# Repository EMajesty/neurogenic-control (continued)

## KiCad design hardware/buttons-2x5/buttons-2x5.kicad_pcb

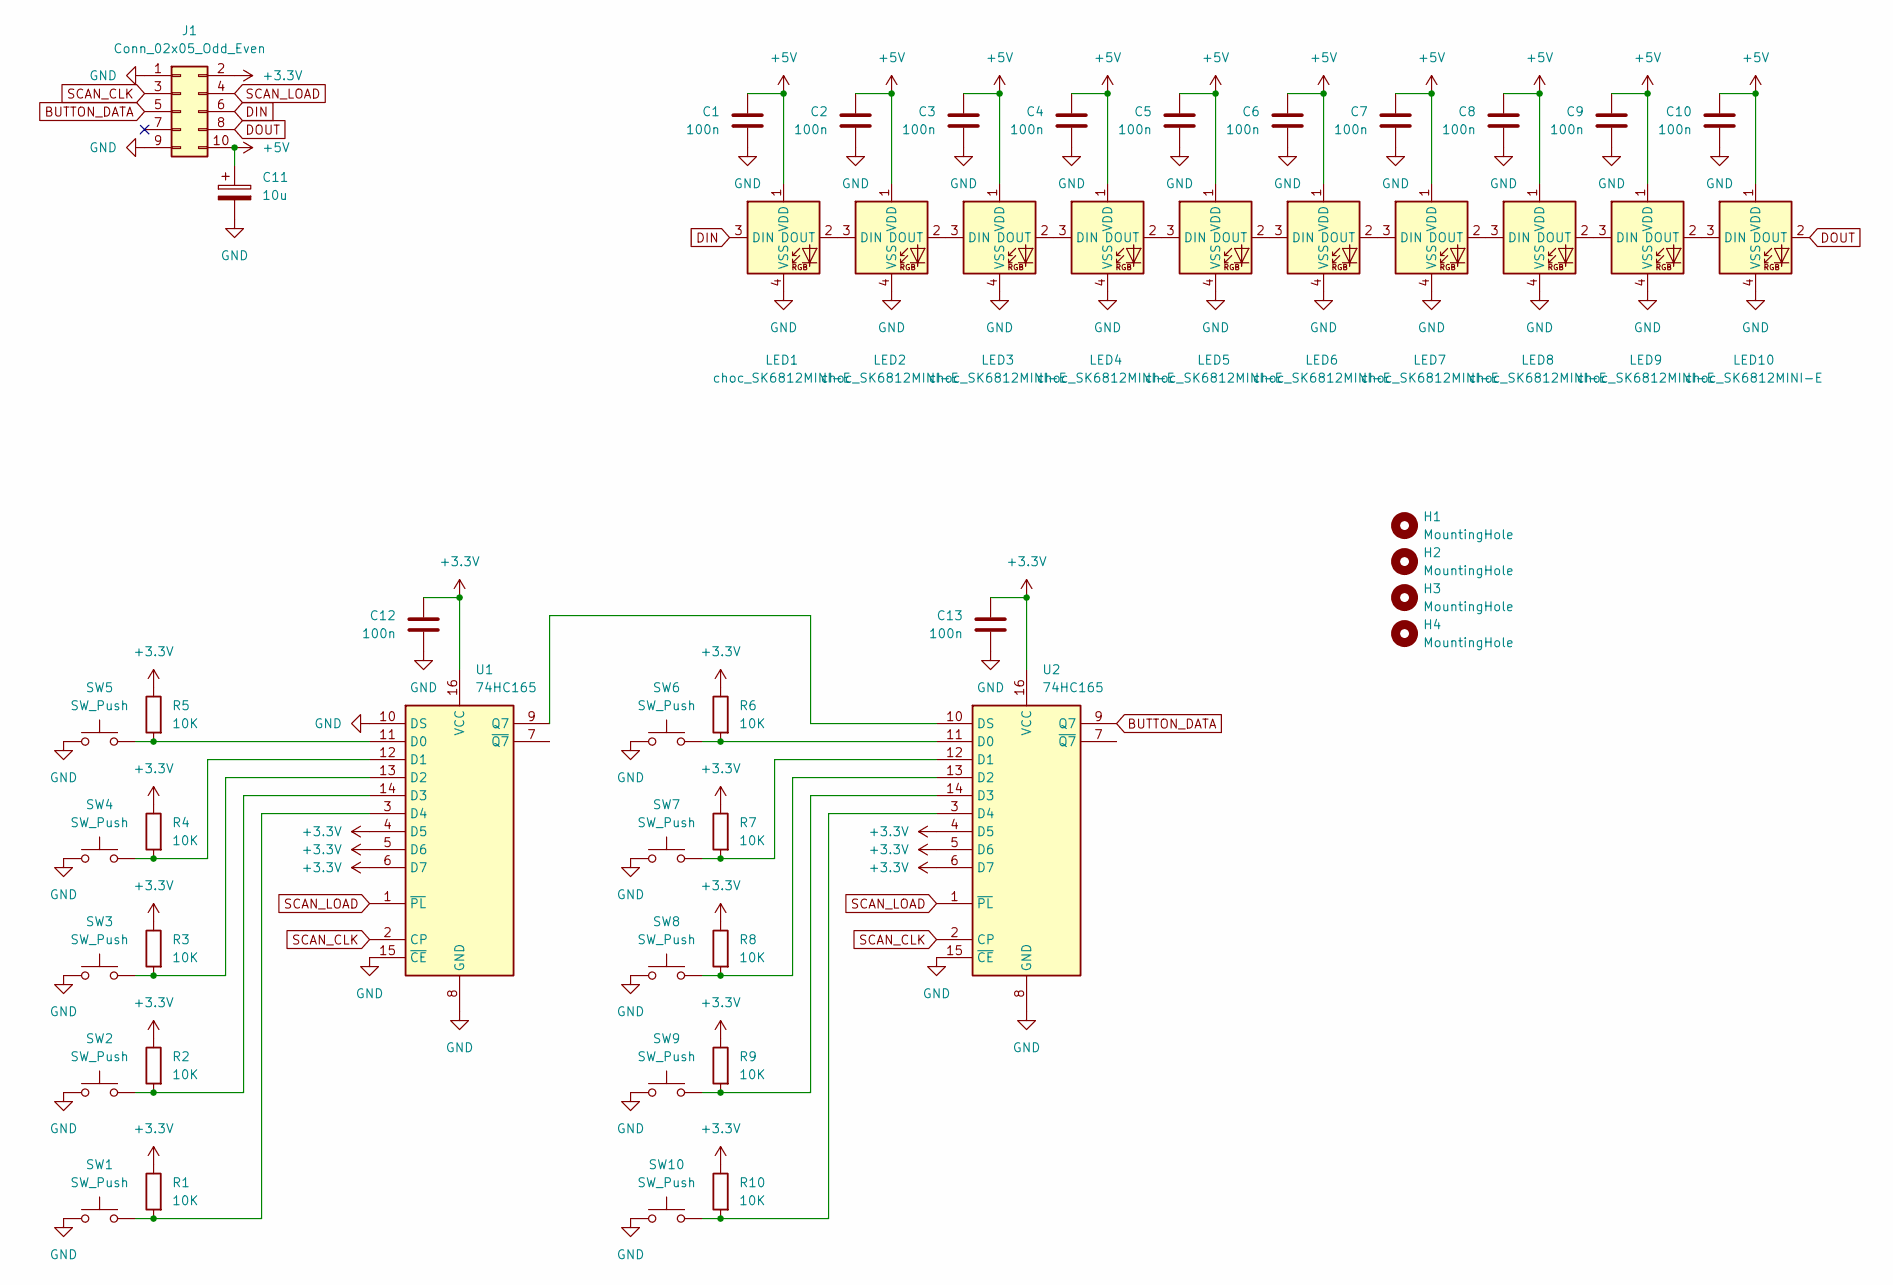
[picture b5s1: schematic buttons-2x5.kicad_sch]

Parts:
C1, C2, C3, C4, C5, C6, C7, C8, C9, C10, C12, C13: 100n; C_0805_2012Metric_Pad1.18x1.45mm_HandSolder
C11: 10u; CP_Radial_D4.0mm_P2.00mm
H1, H2, H3, H4: MountingHole; MountingHole_3.2mm_M3
J1: Conn_02x05_Odd_Even; IDC-Header_2x05_P2.54mm_Vertical
LED1, LED2, LED3, LED4, LED5, LED6, LED7, LED8, LED9, LED10: choc_SK6812MINI-E; LED_choc_6028R-ROT
R1, R2, R3, R4, R5, R6, R7, R8, R9, R10: 10K; R_0805_2012Metric_Pad1.20x1.40mm_HandSolder
SW1, SW2, SW3, SW4, SW5, SW6, SW7, SW8, SW9, SW10: SW_Push; SW_choc_v1_1u
U1, U2: 74HC165; SOIC-16_3.9x9.9mm_P1.27mm

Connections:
+3.3V: C12.1, C13.1, J1.2, R1.1, R2.1, R3.1, R4.1, R5.1, R6.1, R7.1, R8.1, R9.1, R10.1, U1.4 (D5), U1.5 (D6), U1.6 (D7), U1.16 (VCC), U2.4 (D5), U2.5 (D6), U2.6 (D7), U2.16 (VCC)
+5V: C1.1, C2.1, C3.1, C4.1, C5.1, C6.1, C7.1, C8.1, C9.1, C10.1, C11.1, J1.10, LED1.1 (VDD), LED2.1 (VDD), LED3.1 (VDD), LED4.1 (VDD), LED5.1 (VDD), LED6.1 (VDD), LED7.1 (VDD), LED8.1 (VDD), LED9.1 (VDD), LED10.1 (VDD)
BUTTON_DATA: J1.5, U2.9 (Q7)
DIN: J1.6, LED1.3 (DIN)
DOUT: J1.8, LED10.2 (DOUT)
GND: C1.2, C2.2, C3.2, C4.2, C5.2, C6.2, C7.2, C8.2, C9.2, C10.2, C11.2, C12.2, C13.2, J1.1, J1.9, LED1.4 (VSS), LED2.4 (VSS), LED3.4 (VSS), LED4.4 (VSS), LED5.4 (VSS), LED6.4 (VSS), LED7.4 (VSS), LED8.4 (VSS), LED9.4 (VSS), LED10.4 (VSS), SW1.2, SW2.2, SW3.2, SW4.2, SW5.2, SW6.2, SW7.2, SW8.2, SW9.2, SW10.2, U1.8 (GND), U1.10 (DS), U1.15 (~CE), U2.8 (GND), U2.15 (~CE)
unnamed: LED1.2 (DOUT), LED2.3 (DIN)
unnamed: LED2.2 (DOUT), LED3.3 (DIN)
unnamed: LED3.2 (DOUT), LED4.3 (DIN)
unnamed: LED4.2 (DOUT), LED5.3 (DIN)
unnamed: LED5.2 (DOUT), LED6.3 (DIN)
unnamed: LED6.2 (DOUT), LED7.3 (DIN)
unnamed: LED7.2 (DOUT), LED8.3 (DIN)
unnamed: LED8.2 (DOUT), LED9.3 (DIN)
unnamed: LED9.2 (DOUT), LED10.3 (DIN)
unnamed: R5.2, SW5.1, U1.11 (D0)
unnamed: R4.2, SW4.1, U1.12 (D1)
unnamed: R3.2, SW3.1, U1.13 (D2)
unnamed: R2.2, SW2.1, U1.14 (D3)
unnamed: R1.2, SW1.1, U1.3 (D4)
unnamed: U1.9 (Q7), U2.10 (DS)
unnamed: R6.2, SW6.1, U2.11 (D0)
unnamed: R7.2, SW7.1, U2.12 (D1)
unnamed: R8.2, SW8.1, U2.13 (D2)
unnamed: R9.2, SW9.1, U2.14 (D3)
unnamed: R10.2, SW10.1, U2.3 (D4)
SCAN_CLK: J1.3, U1.2 (CP), U2.2 (CP)
SCAN_LOAD: J1.4, U1.1 (~PL), U2.1 (~PL)

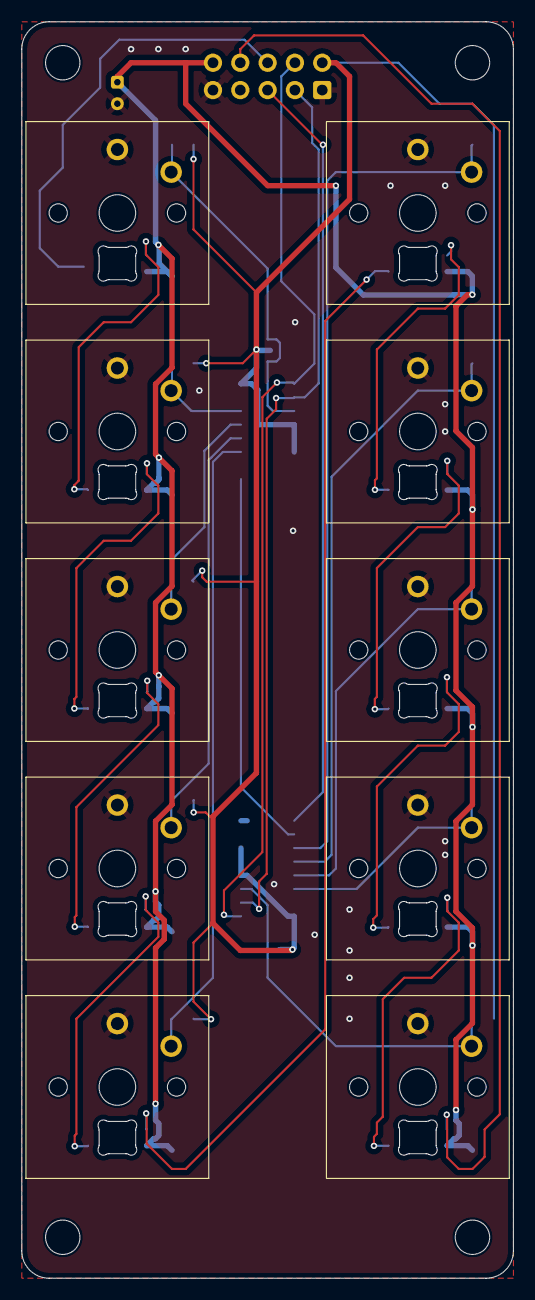
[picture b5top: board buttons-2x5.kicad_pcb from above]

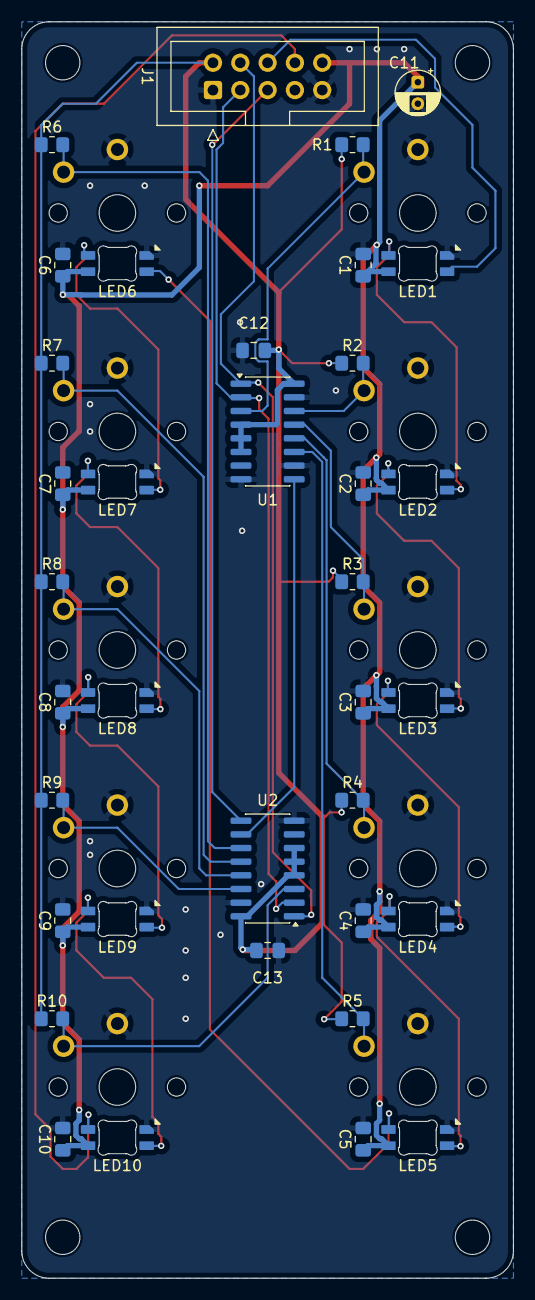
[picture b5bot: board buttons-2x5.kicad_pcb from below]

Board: 2 copper layers, 45.7 x 116.8 mm, 50 parts (36 on the bottom side), 28 nets.

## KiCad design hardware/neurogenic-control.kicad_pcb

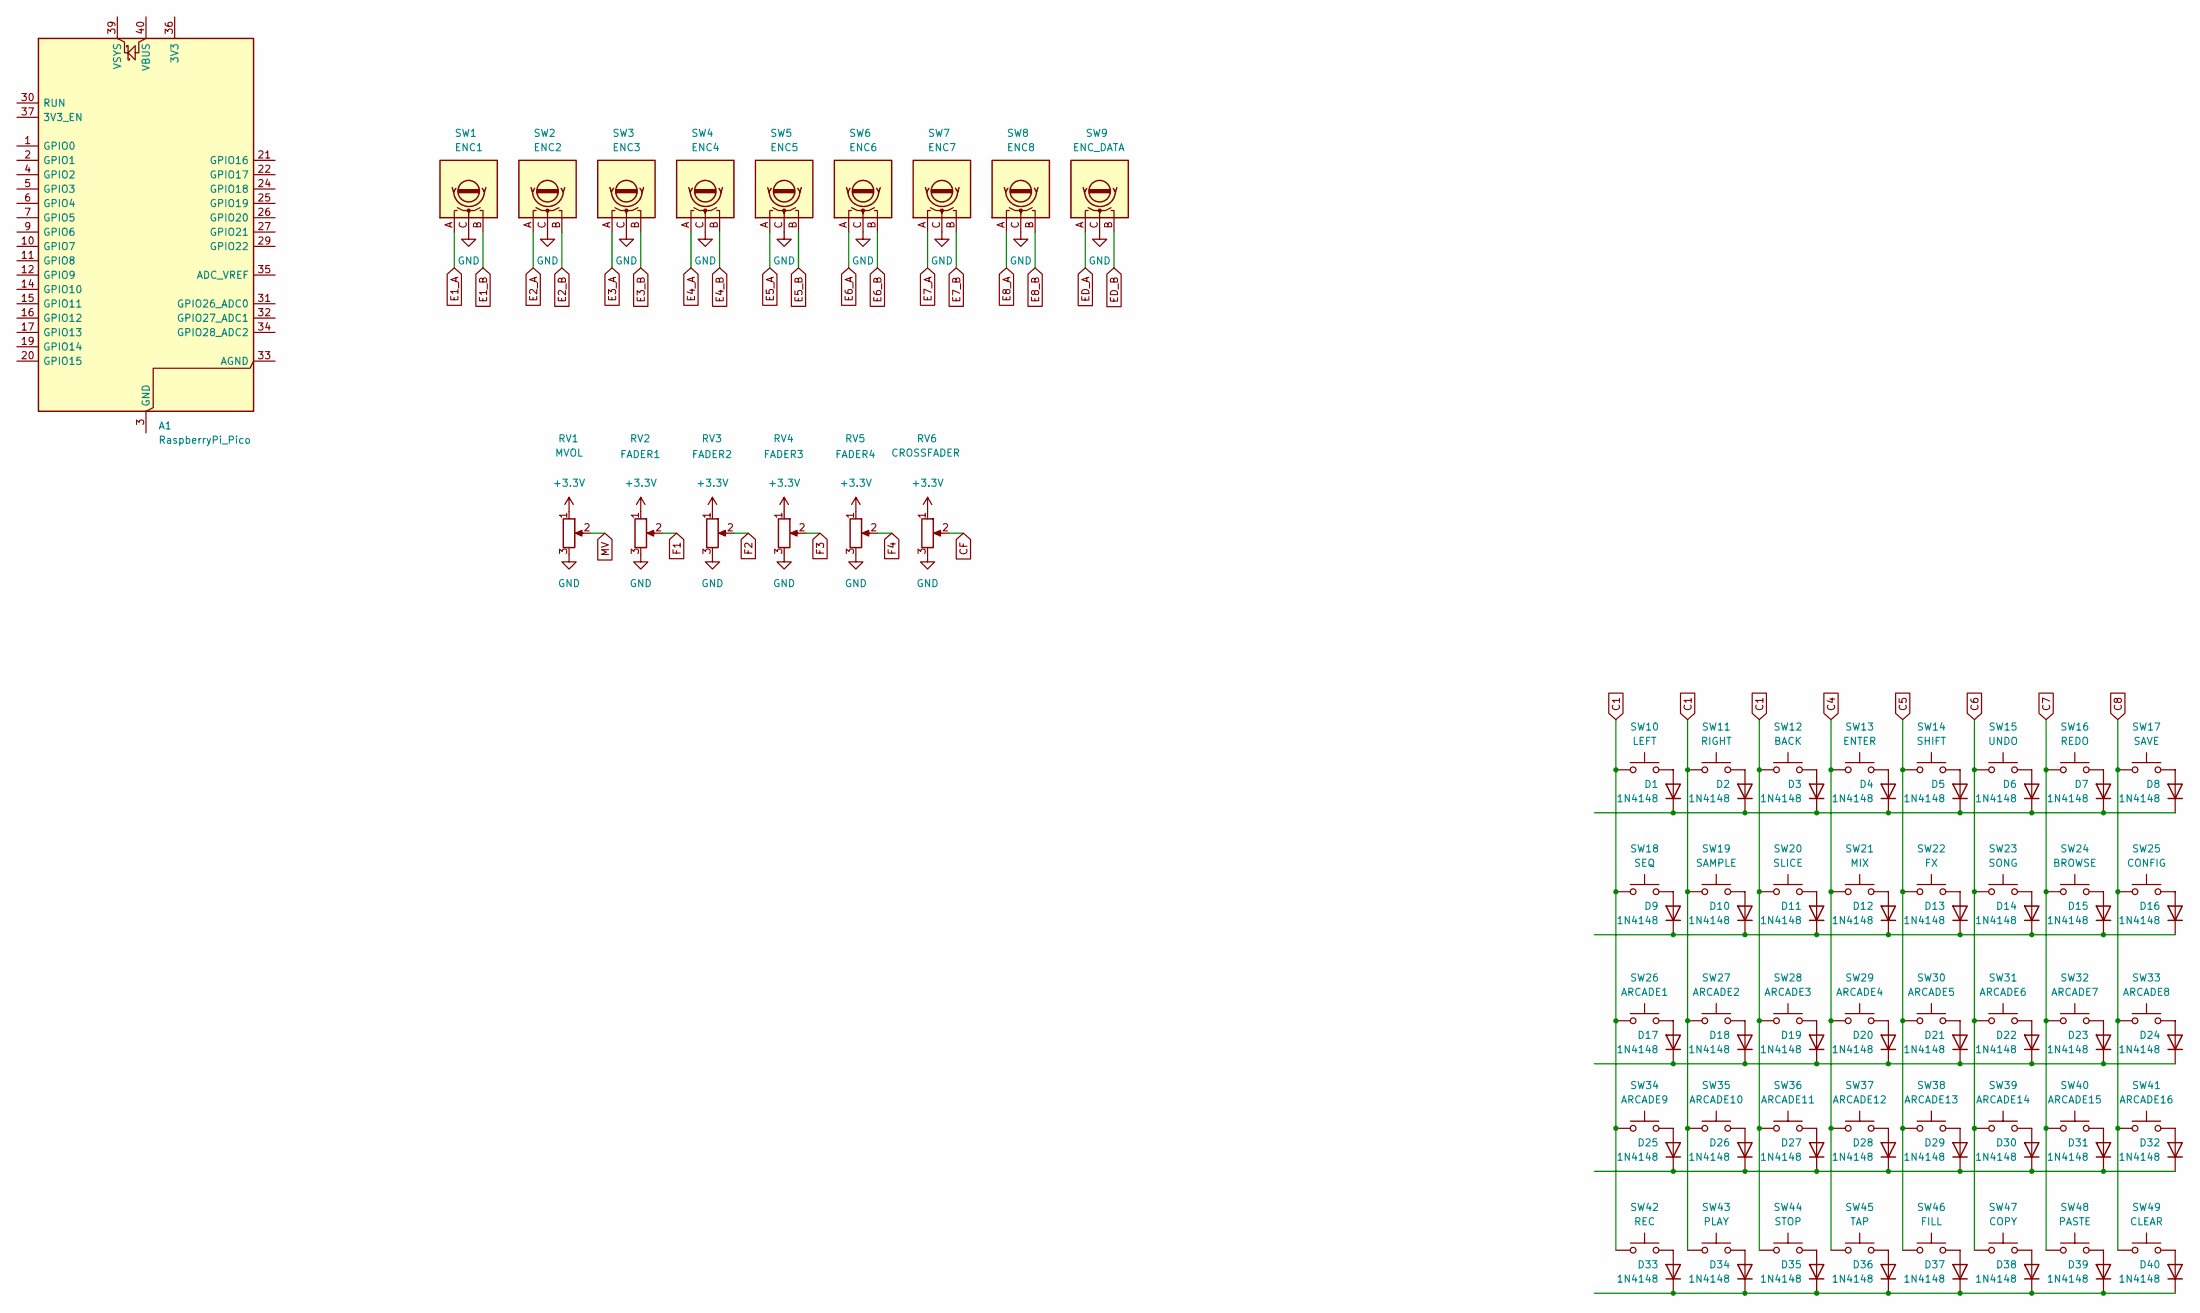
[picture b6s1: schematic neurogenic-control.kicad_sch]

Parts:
A1: RaspberryPi_Pico; RaspberryPi_Pico_Common_Unspecified
D1, D2, D3, D4, D5, D6, D7, D8, D9, D10, D11, D12, D13, D14, D15, D16, D17, D18, D19, D20, D21, D22, D23, D24, D25, D26, D27, D28, D29, D30, D31, D32, D33, D34, D35, D36, D37, D38, D39, D40: 1N4148; D_DO-35_SOD27_P7.62mm_Horizontal
RV1: MVOL
RV2: FADER1
RV3: FADER2
RV4: FADER3
RV5: FADER4
RV6: CROSSFADER
SW1: ENC1; RotaryEncoder_Alps_EC12E_Vertical_H20mm
SW2: ENC2; RotaryEncoder_Alps_EC12E_Vertical_H20mm
SW3: ENC3; RotaryEncoder_Alps_EC12E_Vertical_H20mm
SW4: ENC4; RotaryEncoder_Alps_EC12E_Vertical_H20mm
SW5: ENC5; RotaryEncoder_Alps_EC12E_Vertical_H20mm
SW6: ENC6; RotaryEncoder_Alps_EC12E_Vertical_H20mm
SW7: ENC7; RotaryEncoder_Alps_EC12E_Vertical_H20mm
SW8: ENC8; RotaryEncoder_Alps_EC12E_Vertical_H20mm
SW9: ENC_DATA; RotaryEncoder_Alps_EC12E_Vertical_H20mm
SW10: LEFT; SW_PG1350
SW11: RIGHT; SW_PG1350
SW12: BACK; SW_PG1350
SW13: ENTER; SW_PG1350
SW14: SHIFT; SW_PG1350
SW15: UNDO; SW_PG1350
SW16: REDO; SW_PG1350
SW17: SAVE; SW_PG1350
SW18: SEQ; SW_PG1350
SW19: SAMPLE; SW_PG1350
SW20: SLICE; SW_PG1350
SW21: MIX; SW_PG1350
SW22: FX; SW_PG1350
SW23: SONG; SW_PG1350
SW24: BROWSE; SW_PG1350
SW25: CONFIG; SW_PG1350
SW26: ARCADE1; Arcade_Button_24mm
SW27: ARCADE2; Arcade_Button_24mm
SW28: ARCADE3; Arcade_Button_24mm
SW29: ARCADE4; Arcade_Button_24mm
SW30: ARCADE5; Arcade_Button_24mm
SW31: ARCADE6; Arcade_Button_24mm
SW32: ARCADE7; Arcade_Button_24mm
SW33: ARCADE8; Arcade_Button_24mm
SW34: ARCADE9; Arcade_Button_24mm
SW35: ARCADE10; Arcade_Button_24mm
SW36: ARCADE11; Arcade_Button_24mm
SW37: ARCADE12; Arcade_Button_24mm
SW38: ARCADE13; Arcade_Button_24mm
SW39: ARCADE14; Arcade_Button_24mm
SW40: ARCADE15; Arcade_Button_24mm
SW41: ARCADE16; Arcade_Button_24mm
SW42: REC; SW_PG1350
SW43: PLAY; SW_PG1350
SW44: STOP; SW_PG1350
SW45: TAP; SW_PG1350
SW46: FILL; SW_PG1350
SW47: COPY; SW_PG1350
SW48: PASTE; SW_PG1350
SW49: CLEAR; SW_PG1350

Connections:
C1: SW10.1, SW11.1, SW12.1, SW18.1, SW19.1, SW20.1, SW26.1, SW27.1, SW28.1, SW34.1, SW35.1, SW36.1, SW42.1, SW43.1, SW44.1
C4: SW13.1, SW21.1, SW29.1, SW37.1, SW45.1
C5: SW14.1, SW22.1, SW30.1, SW38.1, SW46.1
C6: SW15.1, SW23.1, SW31.1, SW39.1, SW47.1
C7: SW16.1, SW24.1, SW32.1, SW40.1, SW48.1
C8: SW17.1, SW25.1, SW33.1, SW41.1, SW49.1
E1_A: SW1.A
E1_B: SW1.B
E2_A: SW2.A
E2_B: SW2.B
E3_A: SW3.A
E3_B: SW3.B
E4_A: SW4.A
E4_B: SW4.B
E5_A: SW5.A
E5_B: SW5.B
E6_A: SW6.A
E6_B: SW6.B
E7_A: SW7.A
E7_B: SW7.B
E8_A: SW8.A
E8_B: SW8.B
ED_A: SW9.A
ED_B: SW9.B
GND: RV1.3, RV2.3, RV3.3, RV4.3, RV5.3, RV6.3, SW1.C, SW2.C, SW3.C, SW4.C, SW5.C, SW6.C, SW7.C, SW8.C, SW9.C
unnamed: A1.3 (GND), A1.8 (GND), A1.13 (GND), A1.18 (GND), A1.23 (GND), A1.28 (GND), A1.38 (GND)
unnamed: D1.2 (A), SW10.2
unnamed: D1.1 (K), D2.1 (K), D3.1 (K), D4.1 (K), D5.1 (K), D6.1 (K), D7.1 (K), D8.1 (K)
unnamed: D2.2 (A), SW11.2
unnamed: D3.2 (A), SW12.2
unnamed: D4.2 (A), SW13.2
unnamed: D5.2 (A), SW14.2
unnamed: D6.2 (A), SW15.2
unnamed: D7.2 (A), SW16.2
unnamed: D8.2 (A), SW17.2
unnamed: D9.2 (A), SW18.2
unnamed: D10.2 (A), SW19.2
unnamed: D9.1 (K), D10.1 (K), D11.1 (K), D12.1 (K), D13.1 (K), D14.1 (K), D15.1 (K), D16.1 (K)
unnamed: D11.2 (A), SW20.2
unnamed: D12.2 (A), SW21.2
unnamed: D13.2 (A), SW22.2
unnamed: D14.2 (A), SW23.2
unnamed: D15.2 (A), SW24.2
unnamed: D16.2 (A), SW25.2
unnamed: D17.2 (A), SW26.2
unnamed: D17.1 (K), D18.1 (K), D19.1 (K), D20.1 (K), D21.1 (K), D22.1 (K), D23.1 (K), D24.1 (K)
unnamed: D18.2 (A), SW27.2
unnamed: D19.2 (A), SW28.2
unnamed: D20.2 (A), SW29.2
unnamed: D21.2 (A), SW30.2
unnamed: D22.2 (A), SW31.2
unnamed: D23.2 (A), SW32.2
unnamed: D24.2 (A), SW33.2
unnamed: D25.2 (A), SW34.2
unnamed: D25.1 (K), D26.1 (K), D27.1 (K), D28.1 (K), D29.1 (K), D30.1 (K), D31.1 (K), D32.1 (K)
unnamed: D26.2 (A), SW35.2
unnamed: D27.2 (A), SW36.2
unnamed: D28.2 (A), SW37.2
unnamed: D29.2 (A), SW38.2
unnamed: D30.2 (A), SW39.2
unnamed: D31.2 (A), SW40.2
unnamed: D32.2 (A), SW41.2
unnamed: D33.2 (A), SW42.2
unnamed: D33.1 (K), D34.1 (K), D35.1 (K), D36.1 (K), D37.1 (K), D38.1 (K), D39.1 (K), D40.1 (K)
unnamed: D34.2 (A), SW43.2
unnamed: D35.2 (A), SW44.2
unnamed: D36.2 (A), SW45.2
unnamed: D37.2 (A), SW46.2
unnamed: D38.2 (A), SW47.2
unnamed: D39.2 (A), SW48.2
unnamed: D40.2 (A), SW49.2
unnamed: RV1.1, RV2.1, RV3.1, RV4.1, RV5.1, RV6.1

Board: 2 copper layers, 90 parts (0 on the bottom side), 53 nets, no tracks yet.

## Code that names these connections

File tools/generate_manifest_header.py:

#!/usr/bin/env python3
"""Deterministically generate/check the firmware hardware header."""
import argparse, hashlib, json, pathlib, sys
ROOT=pathlib.Path(__file__).resolve().parents[1]
MANIFEST=ROOT/'hardware/manifest.json'; OUTPUT=ROOT/'firmware/generated/hardware_manifest.hpp'
GPIO_KEYS=('SCAN_CLK','SCAN_LOAD','BUTTON_DATA1','BUTTON_DATA2','BUTTON_DATA3','BUTTON_DATA4','BUTTON_DATA5','BUTTON_DATA6','BUTTON_DATA7','BUTTON_DATA8','BUTTON_DATA9','ENC_LED_DATA','RGB_DATA_RAW','ENC_LED_LATCH','ENC_LED_BLANK')
def validate(m):
    errors=[]
    if m.get('schema_version')!=1: errors.append('schema_version must be 1')
    for key in GPIO_KEYS:
        if not isinstance(m.get('gpio',{}).get(key),int): errors.append(f'missing integer gpio.{key}')
    if len(set(m.get('gpio',{}).values())) != len(m.get('gpio',{})): errors.append('GPIO assignments overlap')
    expected={'buttons-1x8':8,'buttons-2x5':16,'nav':8,'pads':16,'encoders':24}
    for board,bits in expected.items():
        regs=m.get('board_types',{}).get(board,{}).get('registers',[])
        if len(regs)*8!=bits or any(len(r.get('bits',[]))!=8 for r in regs): errors.append(f'{board} chain must contain {bits} bits')
    if m.get('board_types',{}).get('encoders',{}).get('tlc5947',{}).get('bits_per_frame')!=288: errors.append('TLC frame must be 288 bits')
    if errors: raise ValueError('\n'.join(errors))
def render(m):
    fingerprint=hashlib.sha256(MANIFEST.read_bytes()).hexdigest()
    g=m['gpio']; data=[g[f'BUTTON_DATA{i}'] for i in range(1,10)]
    outputs=m['board_types']['encoders']['tlc5947']['outputs']; by_name={name:i for i,name in enumerate(outputs)}
    encoder_map=[[by_name[f'{c}{i}'] for c in 'RGB'] for i in range(1,9)]
    encoder_cpp=','.join('{{{}}}'.format(','.join(map(str,row))) for row in encoder_map)
    encoder_init='{{'+encoder_cpp+'}}'
    type_names=['unused','buttons-1x8','buttons-2x5','nav','pads','encoders']
    bit_rows=[]
    for board in type_names:
        bits=[] if board=='unused' else [bit for reg in m['board_types'][board]['registers'] for bit in reg['bits']]
        bits += ['']*(24-len(bits))
        bit_rows.append('{{{}}}'.format(','.join(json.dumps(x) for x in bits)))
    return f'''#pragma once
// GENERATED by tools/generate_manifest_header.py; do not edit.
#include <array>
#include <cstdint>
namespace ng::hw {{
inline constexpr uint16_t manifest_schema_version = {m['schema_version']};
inline constexpr char manifest_sha256[] = "{fingerprint}";
inline constexpr char hardware_baseline[] = "{m['hardware_baseline']}";
inline constexpr uint8_t scan_clk={g['SCAN_CLK']}, scan_load={g['SCAN_LOAD']};
inline constexpr std::array<uint8_t,9> serial_data={{{','.join(map(str,data))}}};
inline constexpr uint8_t enc_led_data={g['ENC_LED_DATA']}, rgb_data={g['RGB_DATA_RAW']}, enc_led_latch={g['ENC_LED_LATCH']}, enc_led_blank={g['ENC_LED_BLANK']};
inline constexpr uint8_t max_scan_clocks=24;
inline constexpr uint16_t tlc_frame_bits=288;
inline constexpr std::array<std::array<uint8_t,3>,8> encoder_tlc_rgb={encoder_init};
inline constexpr std::array<const char*,6> module_type_name={{{','.join(json.dumps(x) for x in type_names)}}};
inline constexpr std::array<std::array<const char*,24>,6> module_bit_name={{{{{','.join(bit_rows)}}}}};
}}
'''
def main():
    ap=argparse.ArgumentParser(); ap.add_argument('--check',action='store_true'); args=ap.parse_args()
    m=json.loads(MANIFEST.read_text()); validate(m); output=render(m)
    if args.check:
        if not OUTPUT.exists() or OUTPUT.read_text()!=output:
            print(f'stale generated file: {OUTPUT}',file=sys.stderr); return 1
        print('generated manifest header: fresh'); return 0
    OUTPUT.write_text(output); print(f'wrote {OUTPUT}'); return 0
if __name__=='__main__': raise SystemExit(main())

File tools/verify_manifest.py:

#!/usr/bin/env python3
"""Verify the checked manifest against resolved KiCad PCB netlists."""
import argparse, json, pathlib, re, sys
ROOT = pathlib.Path(__file__).resolve().parents[1]

def blocks(text, tag):
    for m in re.finditer(r"\(" + re.escape(tag) + r"\s", text):
        start=m.start(); depth=0; quote=False; escape=False
        for i in range(start, len(text)):
            c=text[i]
            if quote:
                if escape: escape=False
                elif c=="\\": escape=True
                elif c=='"': quote=False
            elif c=='"': quote=True
            elif c=='(': depth += 1
            elif c==')':
                depth -= 1
                if depth == 0: yield text[start:i+1]; break

def pcb_components(board):
    text=(ROOT/f"hardware/{board}/{board}.kicad_pcb").read_text()
    out={}
    for fp in blocks(text,"footprint"):
        rm=re.search(r'\(property "Reference" "([^"]+)"',fp)
        vm=re.search(r'\(property "Value" "([^"]+)"',fp)
        if not rm: continue
        pads={}
        for pad in blocks(fp,"pad"):
            pm=re.match(r'\(pad "([^"]*)"',pad); nm=re.search(r'\(net \d+ "([^"]+)"\)',pad)
            if pm and nm: pads[pm.group(1)]=nm.group(1)
        out[rm.group(1)]={"value":vm.group(1) if vm else "","pads":pads}
    return out

def check(cond,msg,errors):
    if not cond: errors.append(msg)

def schematic_components(path):
    text=path.read_text(); out={}
    for net in blocks(text,'net'):
        name=re.search(r'\(name "([^"]+)"\)',net)
        if not name: continue
        for node in blocks(net,'node'):
            ref=re.search(r'\(ref "([^"]+)"\)',node); pin=re.search(r'\(pin "([^"]+)"\)',node)
            if ref and pin: out.setdefault(ref.group(1),{})[pin.group(1)]=name.group(1)
    return out

def main():
    ap=argparse.ArgumentParser();ap.add_argument('--schematic-dir',type=pathlib.Path);args=ap.parse_args()
    manifest=json.loads((ROOT/'hardware/manifest.json').read_text()); errors=[]
    pcbs={b:pcb_components(b) for b in ('brain','buttons-1x8','buttons-2x5','encoders','nav','pads')}
    pico=pcbs['brain']['A1']['pads']; pico_gpio={0:1,1:2,2:4,3:5,4:6,5:7,6:9,7:10,8:11,9:12,10:14,11:15,12:16,13:17,14:19,15:20,16:21,17:22,18:24,19:25,20:26,21:27,22:29,26:31,27:32,28:34}
    for net,gpio in manifest['gpio'].items():
        expected={'RGB_DATA_RAW':'Net-(A1-GPIO22)','SCAN_CLK':'Net-(A1-GPIO14)','SCAN_LOAD':'Net-(A1-GPIO15)'}.get(net,net)
        check(pico.get(str(pico_gpio[gpio]))==expected,f"GPIO{gpio} {net}: PCB has {pico.get(str(pico_gpio[gpio]))}",errors)
    pin_for_bit=[6,5,4,3,14,13,12,11] # first serial bit through last, QH first
    for board,spec in manifest['board_types'].items():
        for reg in spec.get('registers',[]):
            pads=pcbs[board][reg['ref']]['pads']
            actual=[pads.get(str(pin)) for pin in pin_for_bit]
            declared=reg['bits']
            resolved=[]
            for net in actual:
                if net and ('+3.3V' in net or 'unconnected' in net): resolved.append('NC'); continue
                name=net
                for ref,component in pcbs[board].items():
                    if board=='encoders': continue
                    if not ref.startswith('SW'): continue
                    for pin,pnet in component['pads'].items():
                        if pnet==net and pnet!='GND':
                            name=(f"DATA.{pin}" if board=='nav' and ref=='SW1' else ref)
                resolved.append(name)
            actual=resolved
            check(actual==declared,f"{board}.{reg['ref']} bits: declared {declared}, PCB {actual}",errors)
            check(pads.get('1')=='SCAN_LOAD' and pads.get('2')=='SCAN_CLK',f"{board}.{reg['ref']} clock/load mismatch",errors)
    tlc=pcbs['encoders']['U3']['pads']; declared=manifest['board_types']['encoders']['tlc5947']['outputs']
    check([tlc.get(str(i)) for i in range(5,29)]==declared,"TLC5947 output mapping mismatch",errors)
    check(tlc.get('1')=='GND' and tlc.get('32')=='+3.3V' and tlc.get('3')=='SCAN_CLK',"TLC5947 power/clock mismatch",errors)
    for b in ('buttons-1x8','buttons-2x5','nav','pads'):
        j=pcbs[b]['J1']['pads']
        expected={'1':'GND','2':'+3.3V','3':'SCAN_CLK','4':'SCAN_LOAD','5':'BUTTON_DATA','6':'DIN','9':'GND','10':'+5V'}
        check(all(j.get(pin)==net for pin,net in expected.items()),f"{b}.J1 connector mismatch",errors)
    for port in manifest['brain_ports']:
        j=pcbs['brain'][port['id'].split('.')[1]]['pads']
        check(j.get('1')=='GND' and j.get('2')=='+3.3V' and j.get('3')=='SCAN_CLK' and j.get('4')=='SCAN_LOAD' and j.get('5')==port['data'] and j.get('9')=='GND' and j.get('10')=='+5V',f"{port['id']} connector mismatch",errors)
    check(pcbs['brain']['U2']['pads']=={'1':'+12V','2':'GND','3':'+5V'},"brain.U2 regulator rails mismatch",errors)
    for b in ('buttons-1x8','buttons-2x5','nav'):
        order=manifest['board_types'][b]['rgb_order']; comps=pcbs[b]
        check(all(x in comps for x in order),f"{b} RGB member missing",errors)
    ids=[]
    for board,spec in manifest['board_types'].items():
        for reg in spec.get('registers',[]): ids += [f"{board}:{reg['ref']}:{x}" for x in reg['bits'] if x!='NC']
    check(len(ids)==len(set(ids)),"duplicate qualified physical input",errors)
    check(manifest['assembly']['sk6812_count']==2*8+2*10+6+16,"SK6812 inventory arithmetic mismatch",errors)
    if args.schematic_dir:
        for board,pcb in pcbs.items():
            sch=schematic_components(args.schematic_dir/f'{board}.net')
            for ref in [r for r in pcb if r.startswith(('A','J','U','SW','LED'))]:
                if ref not in sch: continue
                for pin,net in pcb[ref]['pads'].items():
                    if pin in sch[ref]: check(sch[ref][pin]==net,f'{board}.{ref}.{pin}: schematic {sch[ref][pin]} != PCB {net}',errors)
    if errors:
        print("MANIFEST VERIFICATION FAILED",file=sys.stderr)
        for e in errors: print(f"- {e}",file=sys.stderr)
        return 1
    print("manifest: 6 PCB netlists verified; GPIO, chains, inputs, TLC outputs, power/connector invariants OK")
    print("warning: assembly.port_assignment remains UNVERIFIED_HARNESS_ASSIGNMENT")
    if args.schematic_dir: print("schematic: fresh exported component pin nets agree with resolved PCB nets")
    return 0
if __name__=='__main__': raise SystemExit(main())
